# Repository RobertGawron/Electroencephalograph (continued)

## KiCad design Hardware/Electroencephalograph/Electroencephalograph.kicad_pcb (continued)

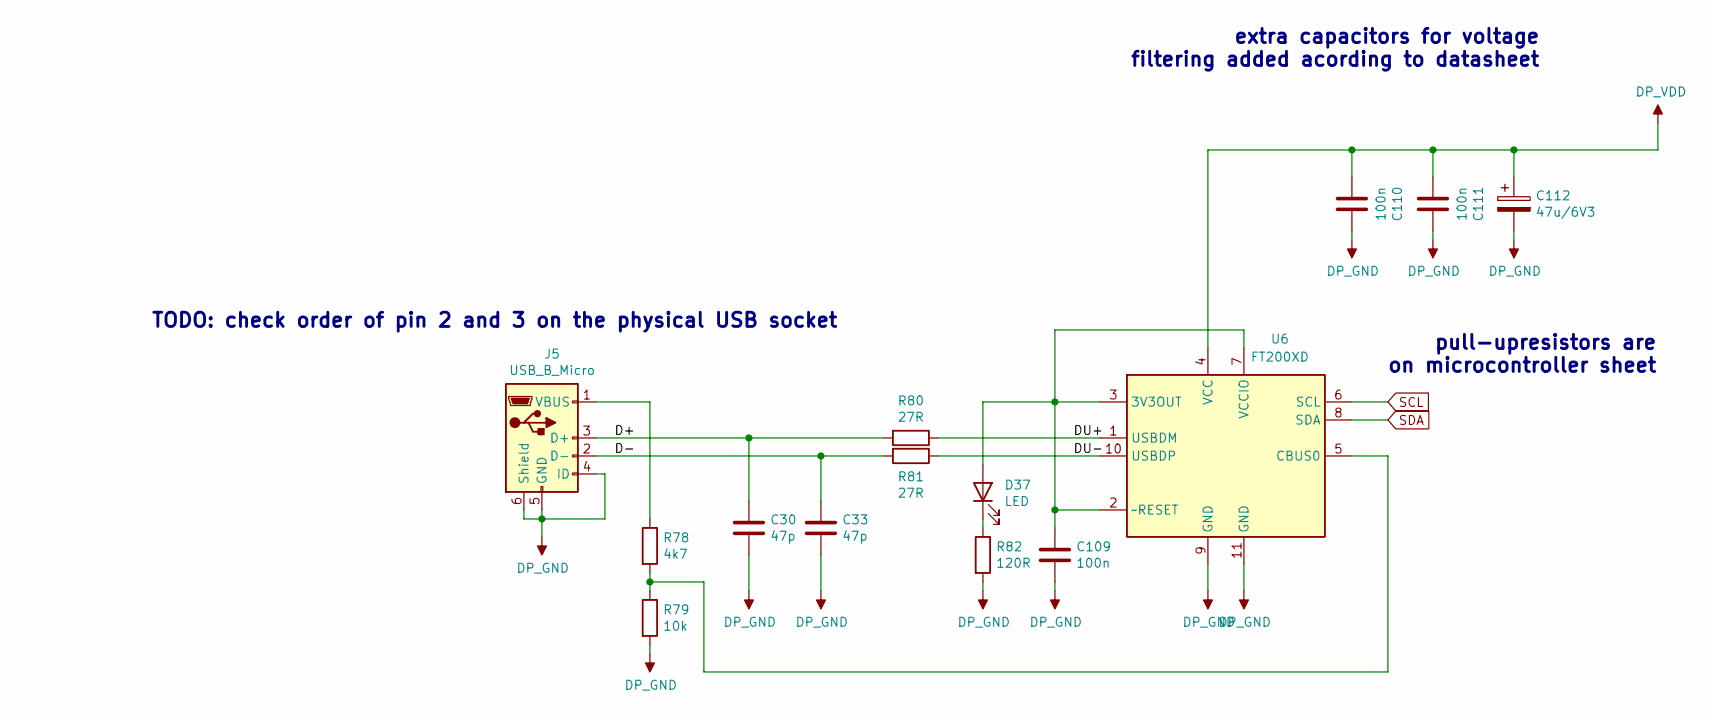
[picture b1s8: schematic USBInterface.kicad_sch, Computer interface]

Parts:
C30, C33: 47p; C_0402_1005Metric
C109, C110, C111: 100n; C_0402_1005Metric
C112: 47u/6V3; CP_EIA-3528-21_Kemet-B
D37: LED; LED_0402_1005Metric
J5: USB_B_Micro; USB_Micro-B_Molex-105017-0001
R78: 4k7; R_0402_1005Metric
R79: 10k; R_0402_1005Metric
R80, R81: 27R; R_0402_1005Metric
R82: 120R; R_0402_1005Metric
U6: FT200XD; DFN-10-1EP_3x3mm_P0.5mm_EP1.55x2.48mm

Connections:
/USBInterface/D+: C30.2, J5.3 (D+), R80.2
/USBInterface/D-: C33.2, J5.2 (D-), R81.2
/USBInterface/DU+: R80.1, U6.1 (USBDM)
/USBInterface/DU-: R81.1, U6.10 (USBDP)
DP_GND: C30.1, C33.1, C109.1, C110.2, C111.2, C112.2, J5.4 (ID), J5.5 (GND), J5.6 (Shield), R79.2, R82.2, U6.9 (GND), U6.11 (GND); also elsewhere on the board
DP_VDD: C110.1, C111.1, C112.1, U6.4 (VCC); also elsewhere on the board
unnamed: C109.2, D37.2 (A), U6.2 (~RESET), U6.3 (3V3OUT), U6.7 (VCCIO)
unnamed: D37.1 (K), R82.1
unnamed: J5.1 (VBUS), R78.1
unnamed: R78.2, R79.1, U6.5 (CBUS0)
SCL: U6.6 (SCL); also elsewhere on the board
SDA: U6.8 (SDA); also elsewhere on the board

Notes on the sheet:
TODO: check order of pin 2 and 3 on the physical USB socket
extra capacitors for voltage filtering added acording to datasheet
pull-upresistors are on microcontroller sheet

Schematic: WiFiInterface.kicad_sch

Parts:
C16: 47u/6V3; CP_EIA-3528-21_Kemet-B
C17, C18: 100n; C_0402_1005Metric
D40, D41: LED; LED_0402_1005Metric
J7: Conn_01x04_Female; PinHeader_1x04_P2.54mm_Vertical
Q1, Q2: FDV304P; SOT-23
R100, R101: 1k; R_0402_1005Metric
R102, R104: 120R; R_0402_1005Metric
R103, R105, R107, R108: 10k; R_0402_1005Metric
R109, R110, R116, R117: 0R; R_0402_1005Metric
U12: ESP-12E

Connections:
CS_ESP: U12.17 (CS0); also elsewhere on the board
DP_GND: C16.2, C17.2, C18.2, J7.1, R100.2, R101.2, R102.2, R104.2, U12.9 (GND); also elsewhere on the board
DP_VDD: Q1.2 (S), Q2.2 (S); also elsewhere on the board
ESP_ENABLE: Q1.1 (G), R100.1; also elsewhere on the board
ESP_FLASH_MODE: R108.2, U12.12 (GPIO0); also elsewhere on the board
ESP_RX: R110.1; also elsewhere on the board
ESP_TX: R109.1; also elsewhere on the board
MISO: U12.18 (MISO); also elsewhere on the board
MOSI: U12.21 (MOSI); also elsewhere on the board
unnamed: C16.1, C17.1, C18.1, J7.4, Q2.3 (D), R103.1, R105.1, R107.1, R108.1, U12.8 (VCC)
unnamed: D40.1 (K), R102.1
unnamed: D40.2 (A), U12.4 (GPIO16)
unnamed: D41.1 (K), R104.1
unnamed: D41.2 (A), U12.5 (GPIO14)
unnamed: J7.2, R116.1
unnamed: J7.3, R117.1
unnamed: Q1.3 (D), Q2.1 (G), R101.1
unnamed: R103.2, U12.3 (CH_PD)
unnamed: R105.2, U12.1 (REST)
unnamed: R107.2, U12.11 (GPIO2)
unnamed: R109.2, R116.2, U12.16 (TXD)
unnamed: R110.2, R117.2, U12.15 (RXD)
SCK: U12.22 (SCLK); also elsewhere on the board

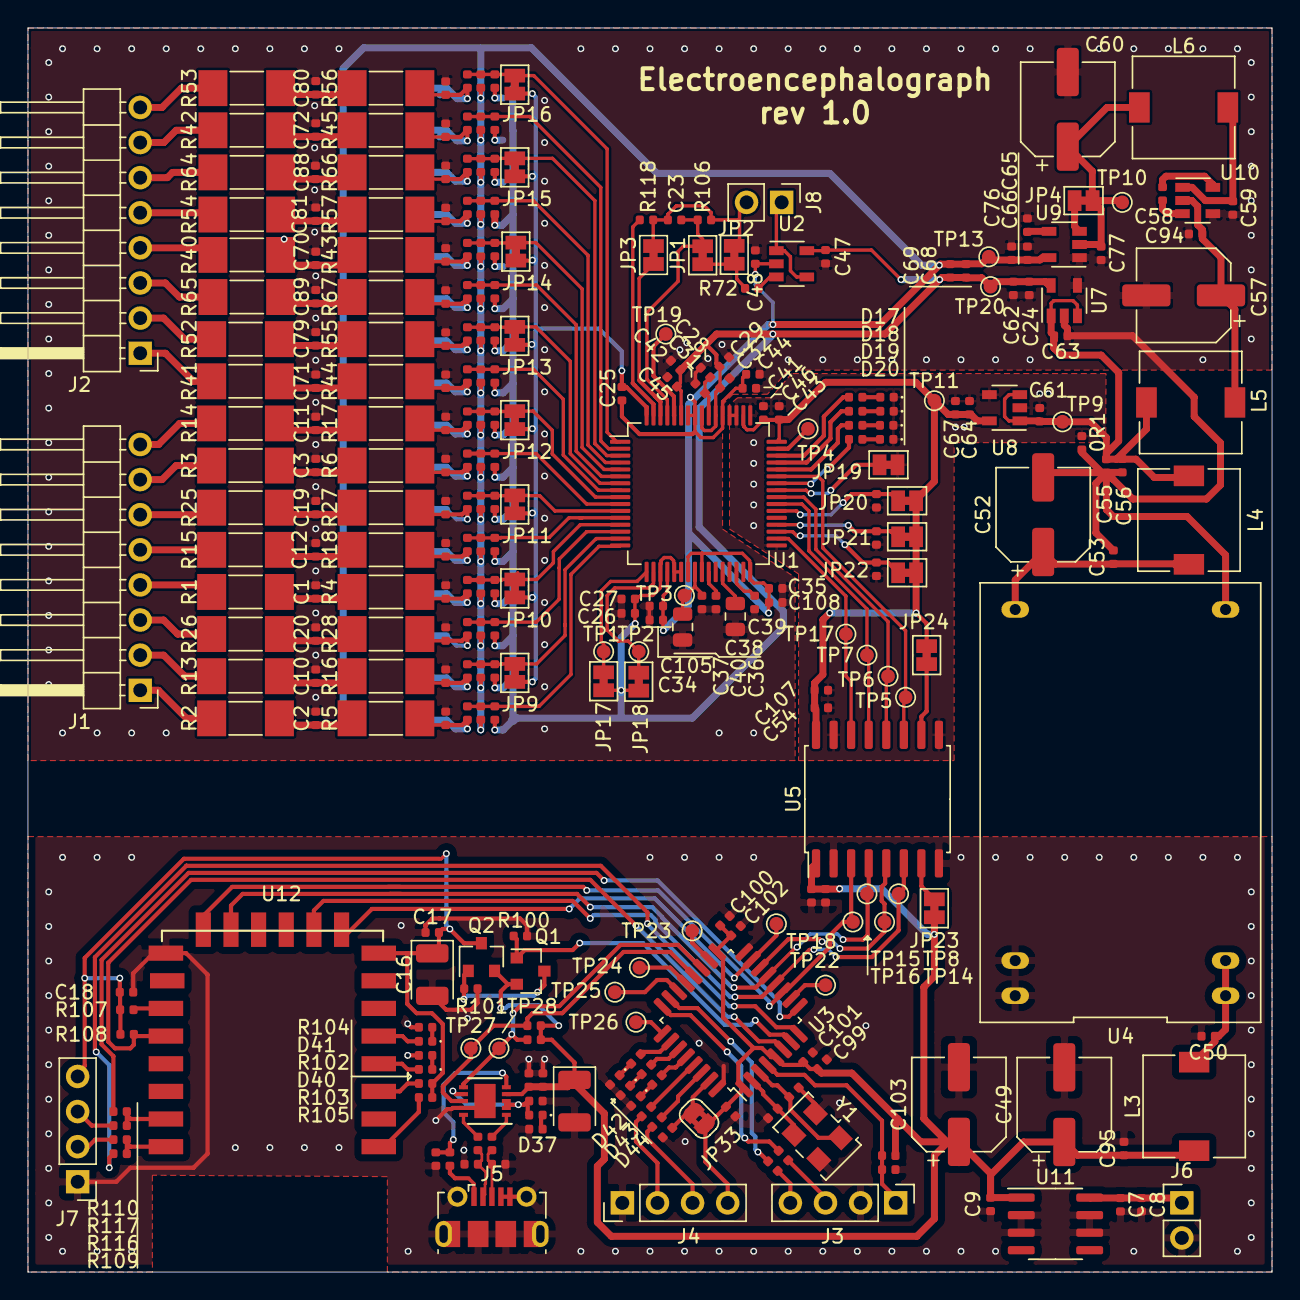
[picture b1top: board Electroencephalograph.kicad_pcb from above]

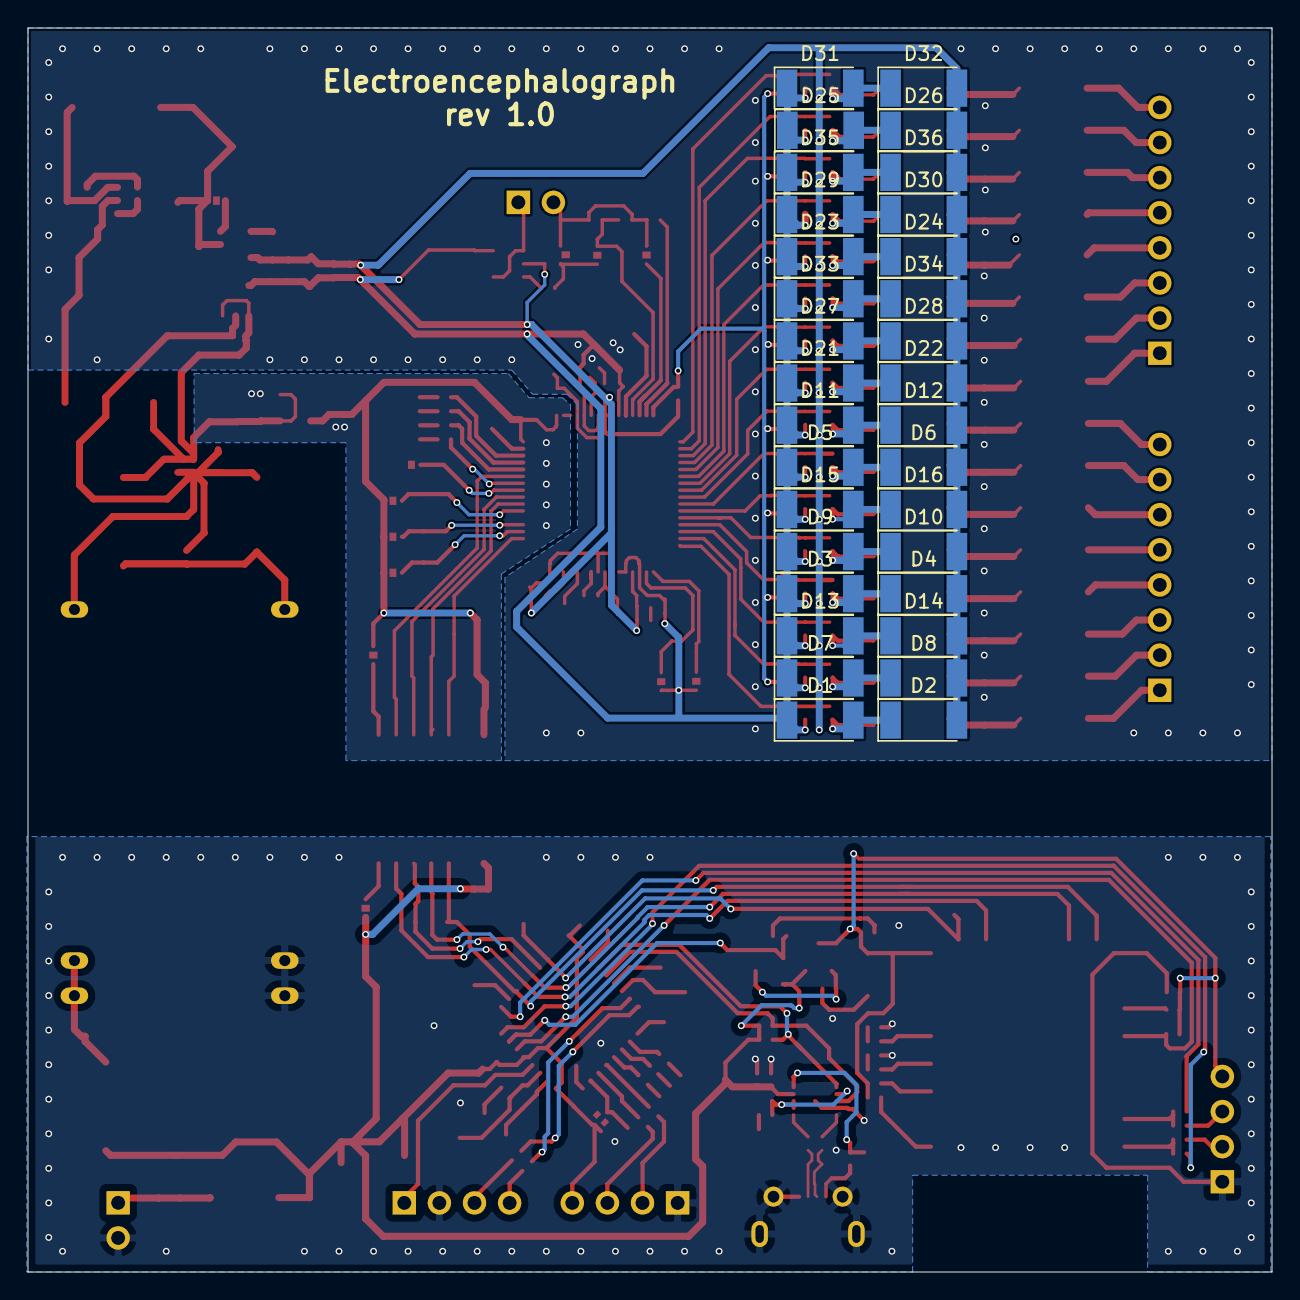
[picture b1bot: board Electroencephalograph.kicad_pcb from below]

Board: 2 copper layers, 90.0 x 90.0 mm, 341 parts (32 on the bottom side), 172 nets.

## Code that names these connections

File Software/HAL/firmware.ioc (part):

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Mcu.Name=STM32F030K6Tx
Mcu.Package=LQFP32
Mcu.UserName=STM32F030K6Tx
PA0.GPIOParameters=GPIO_Label
PA0.GPIO_Label=ESP_FLASH_MODE
PA0.Signal=GPIO_Output
PA1.GPIOParameters=GPIO_Label
PA1.GPIO_Label=ESP_ENABLE
PA1.Signal=GPIO_Output
PA10.Mode=I2C
PA10.Signal=I2C1_SDA
PA2.GPIOParameters=GPIO_Label
PA2.GPIO_Label=ESP_TX
PA2.Signal=GPIO_Output
PA3.GPIOParameters=GPIO_Label
PA3.GPIO_Label=ESP_RX
PA3.Signal=GPIO_Output
PA5.Mode=Full_Duplex_Master
PA5.Signal=SPI1_SCK
PA6.Mode=Full_Duplex_Master
PA6.Signal=SPI1_MISO
PA7.Mode=Full_Duplex_Master
PA7.Signal=SPI1_MOSI
PA9.Mode=I2C
PA9.Signal=I2C1_SCL
PB0.GPIOParameters=GPIO_Label
PB0.GPIO_Label=EEG_CS
PB0.Signal=GPIO_Output
PB1.GPIOParameters=GPIO_Label
PB1.GPIO_Label=CS_ESP
PB1.Signal=GPIO_Output
PB6.Mode=Asynchronous
PB6.Signal=USART1_TX
PB7.Mode=Asynchronous
PB7.Signal=USART1_RX
board=custom

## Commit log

2019-12-12 added ADS1298IPAG element
2019-12-15 paritial routing for analog part
2019-12-21 added spi isolator circuit
2019-12-21 power circuit supply added
2019-12-22 enqable separate electrodes for each point
2019-12-22 added hazard/architecture sections
2019-12-22 added architecture diagrams
2019-12-25 removed external clk and vref
2019-12-25 bom simplification
2019-12-30 draft of PCB routing
2019-12-30 added dc/dc converter 3d model and footprint
2019-12-30 added inductor 3d model
2019-12-30 update 3d model color of the dc/dc converter
2019-12-30 placing power supply on pcb
2019-12-30 added current render to README.md
2019-12-30 fixed urltypo
2019-12-31 placing components groups
2019-12-31 fixed power supply symbols
2019-12-31 fixed gnd clerance
2020-01-01 fixed spi lines
2020-01-01 split of analog and digital ground
2020-01-04 added procesing unit
2020-01-04 render update
2020-01-05 eeg digital part routing
2020-01-07 fixes in filtering caps placing
2020-01-11 routing of analog power supply
2020-01-12 route of analog part, update of 3d render
2020-01-18 generate hal using CubeMX
2020-01-18 further routing
2020-01-19 reshape power supply / acquisition
2020-01-26 minor routing improvements
2020-05-21 placement of usb interface, fix in grounds
2020-05-23 fix #41, fix #18
2020-05-23 fix for missing file
2020-07-04 fix for BOOT pin for MCU
2020-07-04 Squashed 'hardware/kicad-ESP8266/' content from commit 1f3d2c6
    git-subtree-dir: hardware/kicad-ESP8266
    git-subtree-split: 1f3d2c6e49285d4ab4976efc04913bd3974290c1
2020-07-04 add support for esp module
2020-07-04 add missing fixes for esp
2020-07-05 split user interface to separate sheets
2020-07-05 fix esp circuit
2020-07-05 improve mcu component placement on pcb
2020-07-12 draft of mcu routing
2020-07-13 further routing of cpu part
2020-07-14 further routing of mcu part
2020-07-14 add right leg signal, update REDME
2020-07-17 add components for right leg feedback
2020-10-22 Unify folder name convention with my other repos (first upper letter, singular nouns)
2020-10-24 move (for diagrams) from .png to .svg
2020-10-24 move (for diagrams) from .png to .svg - remove obsolete script
2020-10-25 folder structure cleanup, initial project generated from STM32CubeMX (C to Rust transition)
2020-10-25 add project variant for NUCLEO-F091RC, Rust used as programming language, able to build flash and debug the devboard
2020-10-25 prevent github from counting libs for repo language statistic
2020-11-06 Fix grammar mistakes (found by Code Spell Checker add-on in VSCode). (fix #64)
2020-12-16 Fix paths to ESP modules (that changed during directories rename).
2020-12-16 Add grid origin to PCB so that export to FreeCAD works ok. On mechanic overview add top chassis and draft of hole for electrodes sockets, also fixed some dimmensions.
2021-04-17 Add draft of poqer supply routing for digital part.
2021-04-17 Merge pull request #71 from RobertGawron/feature/draft_of_hardware
    Add draft of poqer supply routing for digital part.
2021-04-18 choosed other stgabilisators due to obscolence of previous ones
2021-04-25 Finished design of PCB.
2021-06-27 add bom
2021-08-15 cleanup after transition to KiCad6
